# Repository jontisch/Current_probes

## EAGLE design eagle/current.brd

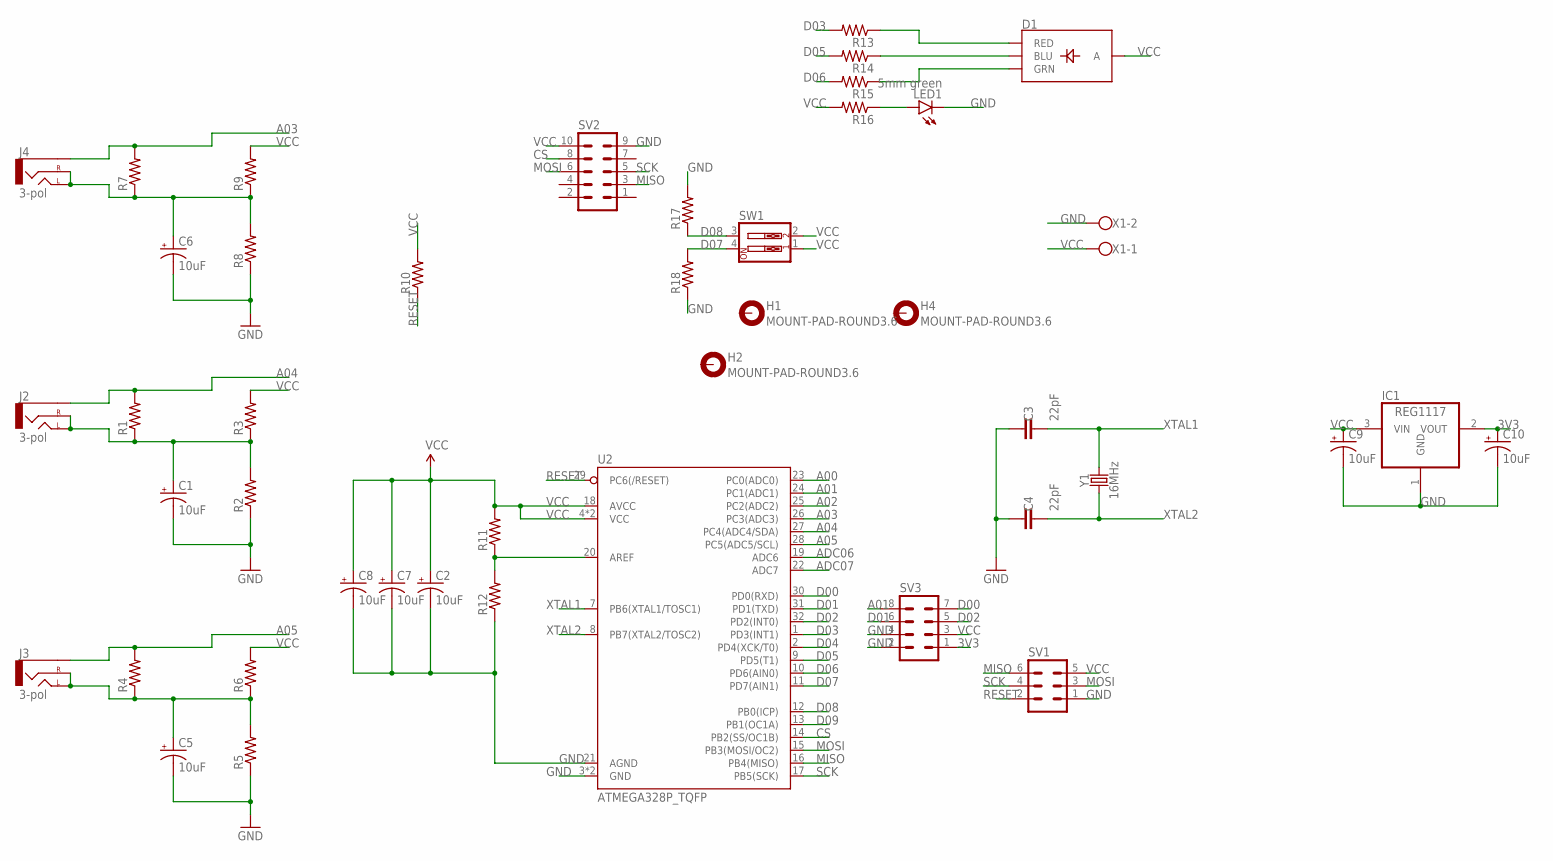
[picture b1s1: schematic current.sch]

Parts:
C1, C2, C5, C6, C7, C8, C9, C10: 10uF; EIA3216
C3, C4: 22pF; 0805
D1: LED-RGB-CASMD; LED-TRICOLOR-SMD
H1, H2, H4: MOUNT-PAD-ROUND3.6; 3,6-PAD
IC1: REG1117; SOT223
J2, J3, J4: 3-pol; AUDIO-JACK
LED1: 5mm green; CHIPLED_0805
R1, R2, R3, R4, R5, R6, R7, R8, R9, R10, R11, R12, R13, R14, R15, R16, R17, R18: 0805
SV1: MA03-2
SV2: MA05-2
SV3: MA04-2
SW1: SW_DIP-2; EDG-02
U2: ATMEGA328P_TQFP; TQFP32-08
X1: W237-102
Y1: 16MHz; CRYSTAL-SMD-3.2X2.5MM

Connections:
3V3: C10.+, IC1.2 (VOUT), SV3.1
A00: U2.23 (PC0(ADC0))
A01: SV3.8, U2.24 (PC1(ADC1))
A02: U2.25 (PC2(ADC2))
A03: J4.SLEEVE, R7.2, U2.26 (PC3(ADC3))
A04: J2.SLEEVE, R1.2, U2.27 (PC4(ADC4/SDA))
A05: J3.SLEEVE, R4.2, U2.28 (PC5(ADC5/SCL))
ADC06: U2.19 (ADC6)
ADC07: U2.22 (ADC7)
CS: SV2.8, U2.14 (PB2(SS/OC1B))
D00: SV3.7, U2.30 (PD0(RXD))
D01: SV3.6, U2.31 (PD1(TXD))
D02: SV3.5, U2.32 (PD2(INT0))
D03: R13.2, U2.1 (PD3(INT1))
D04: U2.2 (PD4(XCK/T0))
D05: R14.2, U2.9 (PD5(T1))
D06: R15.2, U2.10 (PD6(AIN0))
D07: R18.2, SW1.4, U2.11 (PD7(AIN1))
D08: R17.1, SW1.3, U2.12 (PB0(ICP))
D09: U2.13 (PB1(OC1A))
GND: C1.-, C2.-, C3.1, C4.1, C5.-, C6.-, C7.-, C8.-, C9.-, C10.-, IC1.1 (GND), LED1.C, R2.1, R5.1, R8.1, R12.1, R17.2, R18.1, SV1.1, SV2.9, SV3.2, SV3.4, U2.3 (GND), U2.5 (GND), U2.21 (AGND), X1.2
MISO: SV1.6, SV2.3, U2.16 (PB4(MISO))
MOSI: SV1.3, SV2.6, U2.15 (PB3(MOSI/OC2))
unnamed: C5.+, J3.RING (RIGHT), J3.TIP (LEFT), R4.1, R5.2, R6.1
unnamed: C1.+, J2.RING (RIGHT), J2.TIP (LEFT), R1.1, R2.2, R3.1
unnamed: C6.+, J4.RING (RIGHT), J4.TIP (LEFT), R7.1, R8.2, R9.1
unnamed: D1.R (RED), R13.1
unnamed: R11.1, R12.2, U2.20 (AREF)
unnamed: D1.B (BLU), R14.1
unnamed: D1.G (GRN), R15.1
unnamed: LED1.A, R16.1
RESET: R10.1, SV1.2, U2.29 (PC6(/RESET))
SCK: SV1.4, SV2.5, U2.17 (PB5(SCK))
VCC: C2.+, C7.+, C8.+, C9.+, D1.A, IC1.3 (VIN), R3.2, R6.2, R9.2, R10.2, R11.2, R16.2, SV1.5, SV2.10, SV3.3, SW1.1, SW1.2, U2.4 (VCC), U2.6 (VCC), U2.18 (AVCC), X1.1
XTAL1: C3.2, U2.7 (PB6(XTAL1/TOSC1)), Y1.3 (2)
XTAL2: C4.2, U2.8 (PB7(XTAL2/TOSC2)), Y1.1

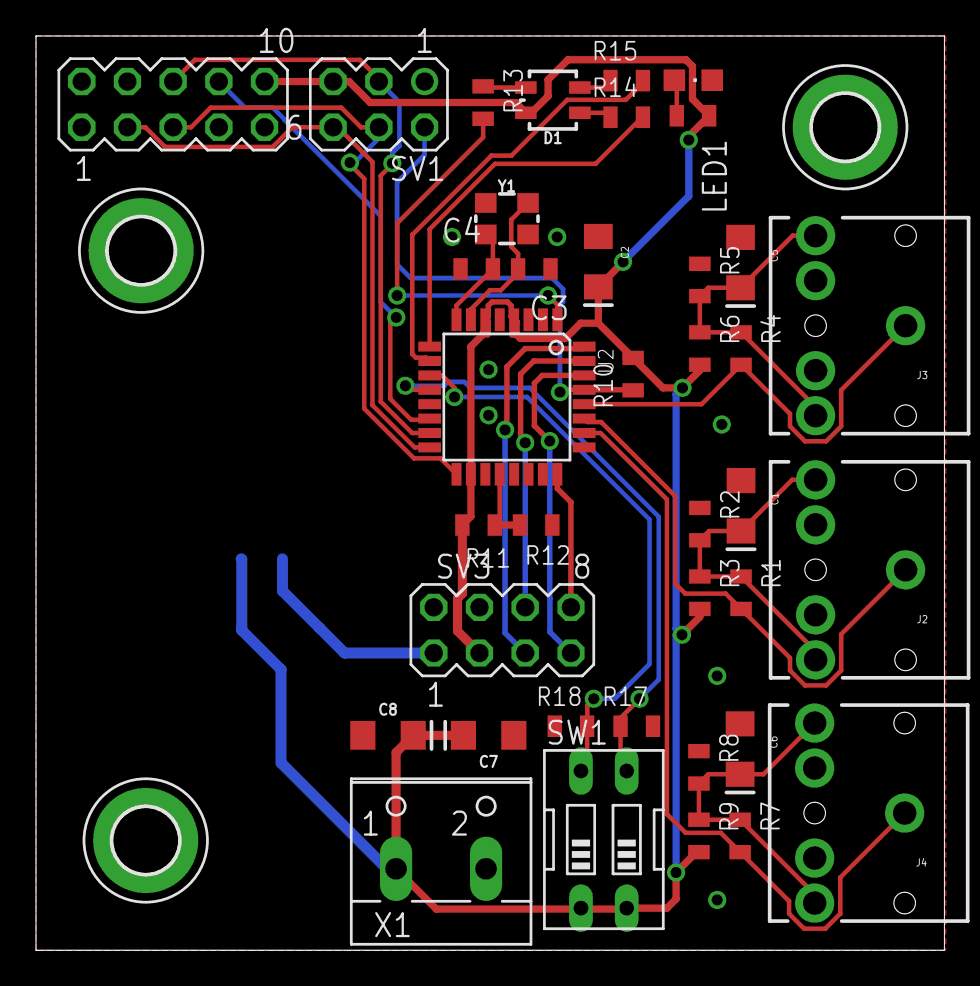
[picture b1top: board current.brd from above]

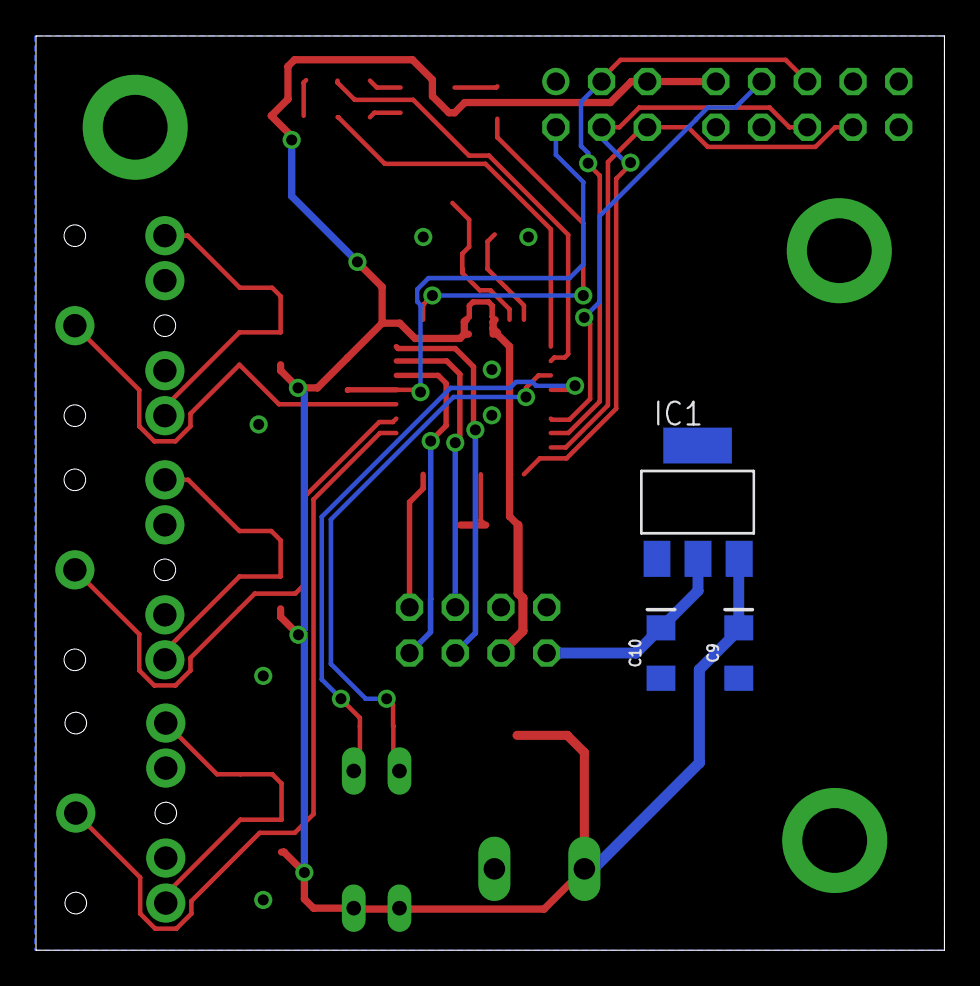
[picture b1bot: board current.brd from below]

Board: 2 copper layers, 50.5 x 50.8 mm, 44 parts (3 on the bottom side), 30 nets.

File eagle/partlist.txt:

Partlist

Exported from current.sch at 2016-11-06 10:24

EAGLE Version 7.7.0 Copyright (c) 1988-2016 CadSoft

Assembly variant: 

Part     Value              Device             Package               Library             Sheet

C1       10uF               CAP_POLPTH1        CPOL-RADIAL-100UF-25V SparkFun-Passives   1
C2       10uF               CAP_POLPTH2        CPOL-RADIAL-10UF-25V  SparkFun-Capacitors 1
C3       22pF               C5/2.5             C5B2.5                capacitor-wima      1
C4       22pF               C5/2.5             C5B2.5                capacitor-wima      1
C5       10uF               CAP_POLPTH1        CPOL-RADIAL-100UF-25V SparkFun-Passives   1
C6       10uF               CAP_POLPTH1        CPOL-RADIAL-100UF-25V SparkFun-Passives   1
H1       MOUNT-PAD-ROUND3.6 MOUNT-PAD-ROUND3.6 3,6-PAD               holes               1
J1       USB-MICROB         USB-MICROB         USB-MICROB            SparkFun-Connectors 1
J2       3-pol              AUDIO-JACKPTH      AUDIO-JACK            SparkFun-Connectors 1
J3       3-pol              AUDIO-JACKPTH      AUDIO-JACK            SparkFun-Connectors 1
J4       3-pol              AUDIO-JACKPTH      AUDIO-JACK            SparkFun-Connectors 1
LED1     5mm green          LED5MM             LED5MM                led                 1
Q1       16MHz              XTAL/S             QS                    special             1
R1       33                 R-US_0204/5        0204/5                resistor            1
R2       10K                R-US_0204/5        0204/5                resistor            1
R3       10K                R-US_0204/5        0204/5                resistor            1
R4       33                 R-US_0204/5        0204/5                resistor            1
R5       10K                R-US_0204/5        0204/5                resistor            1
R6       10K                R-US_0204/5        0204/5                resistor            1
R7       33                 R-US_0204/5        0204/5                resistor            1
R8       10K                R-US_0204/5        0204/5                resistor            1
R9       10K                R-US_0204/5        0204/5                resistor            1
R10      10K                R-US_0204/5        0204/5                resistor            1
R11      10K                R-US_0204/5        0204/5                resistor            1
R12      10K                R-US_0204/5        0204/5                resistor            1
R13      180                R-US_0204/5        0204/5                resistor            1
R14      100                R-US_0204/5        0204/5                resistor            1
R15      470                R-US_0204/5        0204/5                resistor            1
R16      100                R-US_0204/5        0204/5                resistor            1
R17      10K                R-US_0204/5        0204/5                resistor            1
R18      10K                R-US_0204/5        0204/5                resistor            1
SV1                         MA03-2             MA03-2                con-lstb            1
SV2                         MA05-2             MA05-2                con-lstb            1
SV3      rgb-led            MA04-1             MA04-1                con-lstb            1
SW1                         SW_DIP-2           EDG-02                special             1
U1       ATMEGA328P_PDIP    ATMEGA328P_PDIP    DIL28-3               SparkFun-DigitalIC  1

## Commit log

2020-01-31 Board upgrades

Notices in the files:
parts and their libraries:
SparkFun-Connectors: Licensing: Creative Commons ShareAlike 4.0 International - https://creativecommons.org/licenses/by-sa/4.0
